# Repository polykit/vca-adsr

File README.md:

# Polykit VCA-ADSR

This repository contains schematics and PCB layout for a board with a VCA and an ADSR on it.

## Schematics

### VCA

### ADSR

## References

https://www.schmitzbits.de/adsr.html

https://yusynth.net/Modular/EN/VCA/index.html

https://kassu2000.blogspot.com/2015/10/vca.html

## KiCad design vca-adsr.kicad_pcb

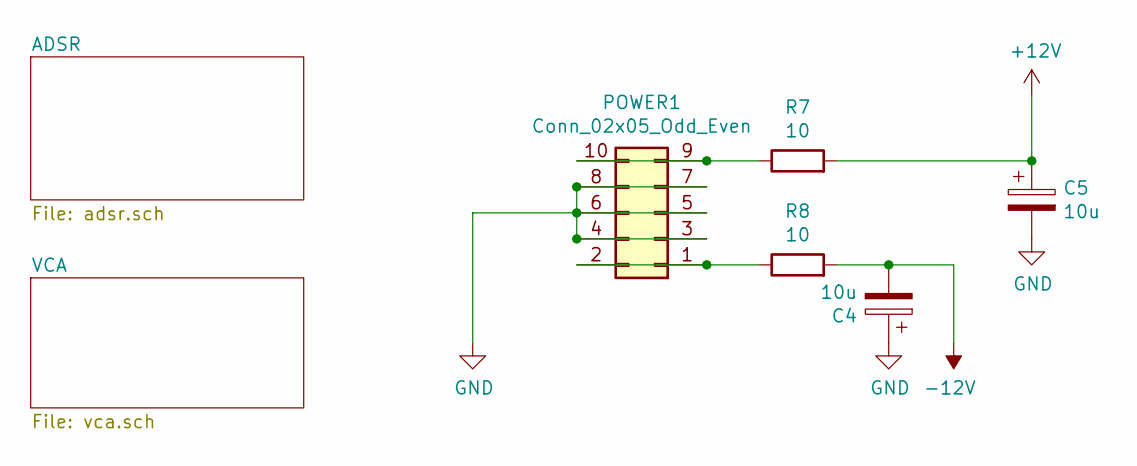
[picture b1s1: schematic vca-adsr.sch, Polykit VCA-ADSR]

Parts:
C4, C5: 10u; CP_Radial_D5.0mm_P2.50mm
POWER1: Conn_02x05_Odd_Even; IDC-Header_2x05_P2.54mm_Vertical
R7, R8: 10; R_Axial_DIN0207_L6.3mm_D2.5mm_P7.62mm_Horizontal

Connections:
+12V: C5.1, R7.2; also elsewhere on the board
-12V: C4.2, R8.2; also elsewhere on the board
GND: C4.1, C5.2, POWER1.3, POWER1.4, POWER1.5, POWER1.6, POWER1.7, POWER1.8; also elsewhere on the board
unnamed: POWER1.1, POWER1.2, R8.1
unnamed: POWER1.9, POWER1.10, R7.1

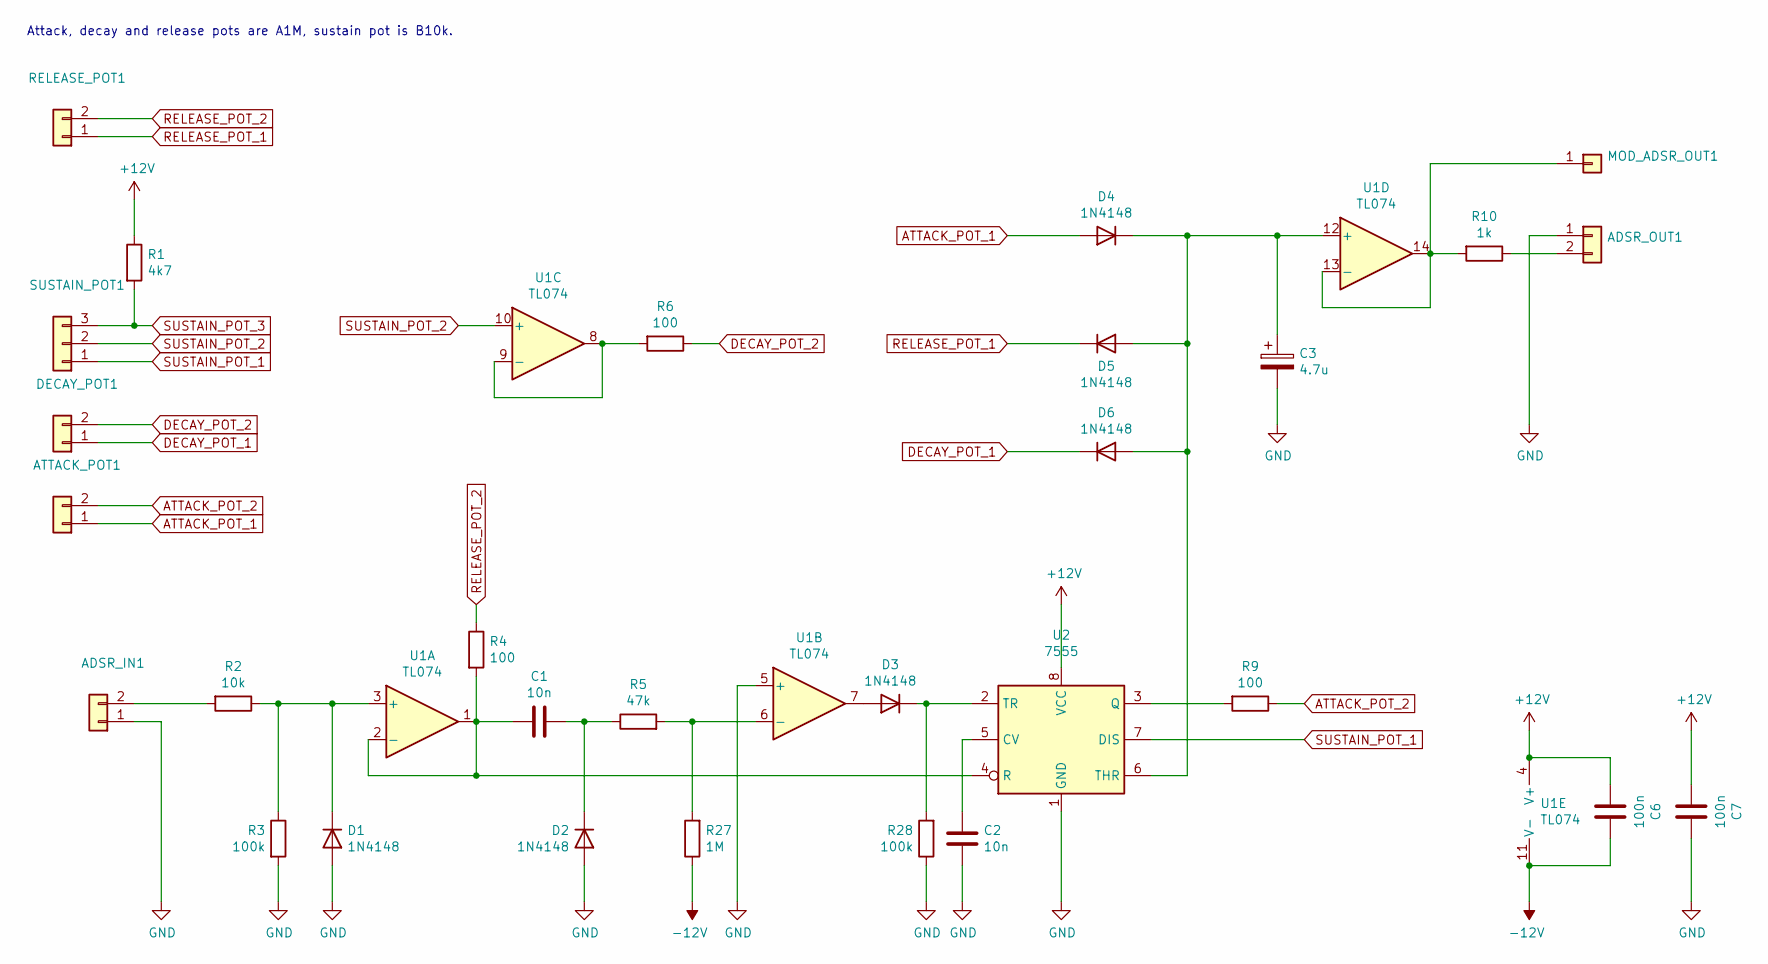
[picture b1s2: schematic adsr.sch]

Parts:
ADSR_IN1: Conn_01x02; Molex_KK-254_AE-6410-02A_1x02_P2.54mm_Vertical
ADSR_OUT1: Conn_01x02; Molex_KK-254_AE-6410-02A_1x02_P2.54mm_Vertical
ATTACK_POT1: Conn_01x02; Molex_KK-254_AE-6410-02A_1x02_P2.54mm_Vertical
C1, C2: 10n; C_Disc_D5.0mm_W2.5mm_P5.00mm
C3: 4.7u; CP_Radial_D5.0mm_P2.50mm
C6, C7: 100n; C_Disc_D5.0mm_W2.5mm_P5.00mm
D1, D2, D3, D4, D5, D6: 1N4148; D_DO-35_SOD27_P7.62mm_Horizontal
DECAY_POT1: Conn_01x02; Molex_KK-254_AE-6410-02A_1x02_P2.54mm_Vertical
MOD_ADSR_OUT1: Conn_01x01; Pin_D0.7mm_L6.5mm_W1.8mm_FlatFork
R1: 4k7; R_Axial_DIN0207_L6.3mm_D2.5mm_P7.62mm_Horizontal
R2: 10k; R_Axial_DIN0207_L6.3mm_D2.5mm_P7.62mm_Horizontal
R3: 100k; R_Axial_DIN0207_L6.3mm_D2.5mm_P7.62mm_Horizontal
R4: 100; R_Axial_DIN0207_L6.3mm_D2.5mm_P2.54mm_Vertical
R5: 47k; R_Axial_DIN0207_L6.3mm_D2.5mm_P2.54mm_Vertical
R6, R9: 100; R_Axial_DIN0207_L6.3mm_D2.5mm_P7.62mm_Horizontal
R10: 1k; R_Axial_DIN0207_L6.3mm_D2.5mm_P7.62mm_Horizontal
R27: 1M; R_Axial_DIN0207_L6.3mm_D2.5mm_P2.54mm_Vertical
R28: 100k; R_Axial_DIN0207_L6.3mm_D2.5mm_P2.54mm_Vertical
RELEASE_POT1: Conn_01x02; Molex_KK-254_AE-6410-02A_1x02_P2.54mm_Vertical
SUSTAIN_POT1: Conn_01x02; Molex_KK-254_AE-6410-03A_1x03_P2.54mm_Vertical
U1: TL074; DIP-14_W7.62mm_LongPads
U2: 7555; DIP-8_W7.62mm_LongPads

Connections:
+12V: C6.2, C7.2, R1.1, U1.4 (V+), U2.8 (VCC); also elsewhere on the board
-12V: C6.1, R27.1, U1.11 (V-); also elsewhere on the board
ATTACK_POT_1: ATTACK_POT1.1, D4.2 (A)
ATTACK_POT_2: ATTACK_POT1.2, R9.1
DECAY_POT_1: D6.1 (K), DECAY_POT1.1
DECAY_POT_2: DECAY_POT1.2, R6.1
GND: ADSR_IN1.1, ADSR_OUT1.1, C2.1, C3.2, C7.1, D1.2 (A), D2.2 (A), R3.2, R28.1, U1.5 (+), U2.1 (GND); also elsewhere on the board
unnamed: ADSR_IN1.2, R2.2
unnamed: ADSR_OUT1.2, R10.1
unnamed: C1.1, D2.1 (K), R5.1
unnamed: C1.2, R4.2, U1.1, U1.2 (-), U2.4 (R)
unnamed: C2.2, U2.5 (CV)
unnamed: C3.1, D4.1 (K), D5.2 (A), D6.2 (A), U1.12 (+), U2.6 (THR)
unnamed: D1.1 (K), R2.1, R3.1, U1.3 (+)
unnamed: D3.1 (K), R28.2, U2.2 (TR)
unnamed: D3.2 (A), U1.7
unnamed 20: MOD_ADSR_OUT1.1, R10.2, U1.13 (-), U1.14; also elsewhere on the board
unnamed: R6.2, U1.8, U1.9 (-)
unnamed: R9.2, U2.3 (Q)
unnamed: R5.2, R27.2, U1.6 (-)
RELEASE_POT_1: D5.1 (K), RELEASE_POT1.1
RELEASE_POT_2: R4.1, RELEASE_POT1.2
SUSTAIN_POT_1: SUSTAIN_POT1.1, U2.7 (DIS)
SUSTAIN_POT_2: SUSTAIN_POT1.2, U1.10 (+)
SUSTAIN_POT_3: R1.2, SUSTAIN_POT1.3

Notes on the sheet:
Attack, decay and release pots are A1M, sustain pot is B10k.

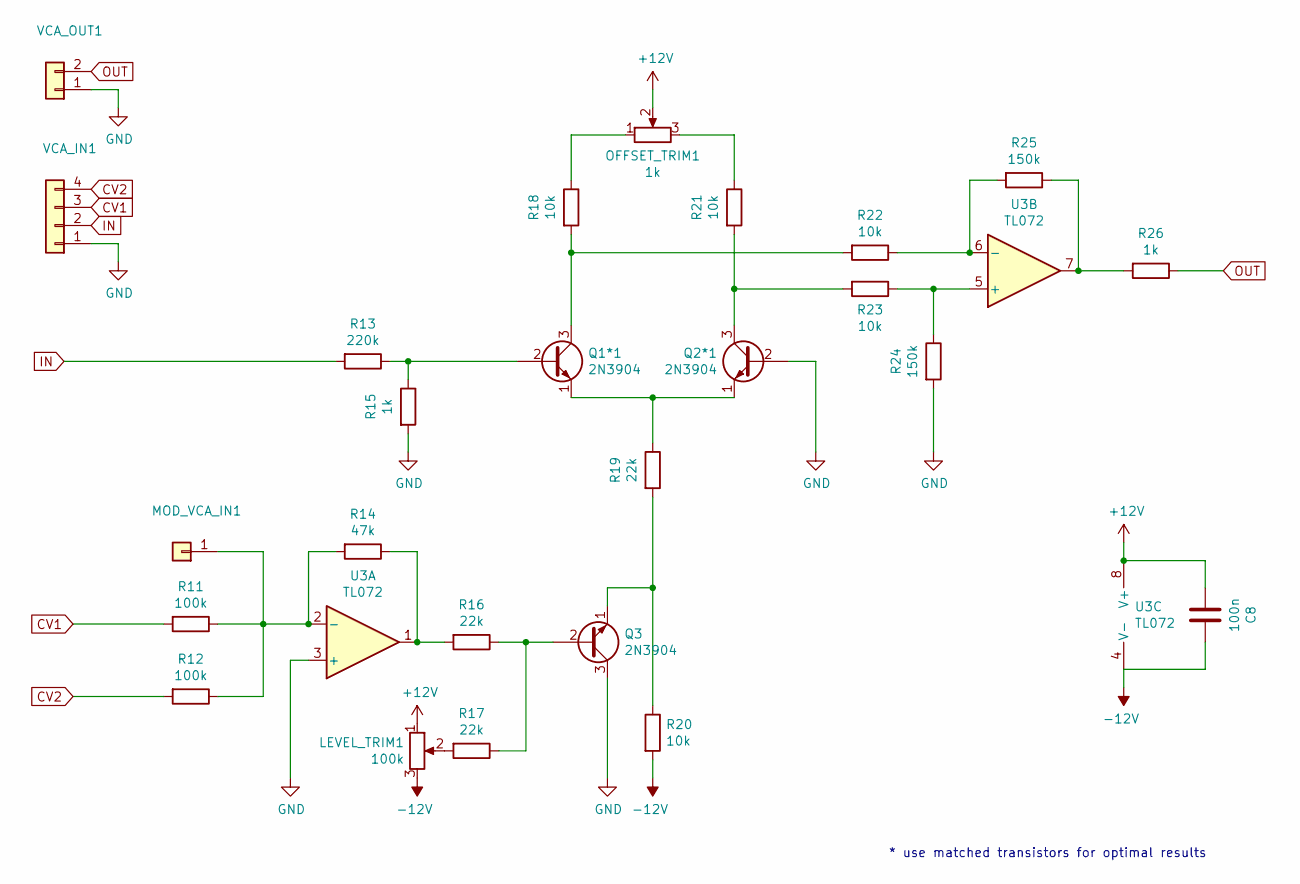
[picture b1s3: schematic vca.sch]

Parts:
C8: 100n; C_Disc_D5.0mm_W2.5mm_P5.00mm
LEVEL_TRIM1: 100k; Potentiometer_ACP_CA9-H5_Horizontal
MOD_VCA_IN1: Conn_01x01; Pin_D0.7mm_L6.5mm_W1.8mm_FlatFork
OFFSET_TRIM1: 1k; Potentiometer_ACP_CA9-H5_Horizontal
Q1*1, Q2*1, Q3: 2N3904; TO-92_Inline_Wide
R11, R12: 100k; R_Axial_DIN0207_L6.3mm_D2.5mm_P7.62mm_Horizontal
R13: 220k; R_Axial_DIN0207_L6.3mm_D2.5mm_P7.62mm_Horizontal
R14: 47k; R_Axial_DIN0207_L6.3mm_D2.5mm_P7.62mm_Horizontal
R15, R26: 1k; R_Axial_DIN0207_L6.3mm_D2.5mm_P7.62mm_Horizontal
R16, R17, R19: 22k; R_Axial_DIN0207_L6.3mm_D2.5mm_P7.62mm_Horizontal
R18, R20, R21, R22, R23: 10k; R_Axial_DIN0207_L6.3mm_D2.5mm_P7.62mm_Horizontal
R24, R25: 150k; R_Axial_DIN0207_L6.3mm_D2.5mm_P7.62mm_Horizontal
U3: TL072; DIP-8_W7.62mm_Socket_LongPads
VCA_IN1: Conn_01x04; Molex_KK-254_AE-6410-04A_1x04_P2.54mm_Vertical
VCA_OUT1: Conn_01x02; Molex_KK-254_AE-6410-02A_1x02_P2.54mm_Vertical

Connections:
+12V: C8.2, LEVEL_TRIM1.1, OFFSET_TRIM1.2, U3.8 (V+); also elsewhere on the board
-12V: C8.1, LEVEL_TRIM1.3, R20.2, U3.4 (V-); also elsewhere on the board
CV1: R11.2, VCA_IN1.3
CV2: R12.2, VCA_IN1.4
GND: Q2*1.2 (B), Q3.3 (C), R15.2, R24.2, U3.3 (+), VCA_IN1.1, VCA_OUT1.1; also elsewhere on the board
IN: R13.2, VCA_IN1.2
unnamed: LEVEL_TRIM1.2, R17.2
unnamed 21: MOD_VCA_IN1.1, R11.1, R12.1, R14.2, U3.2 (-); also elsewhere on the board
unnamed: OFFSET_TRIM1.1, R18.1
unnamed: OFFSET_TRIM1.3, R21.1
unnamed: Q1*1.1 (E), Q2*1.1 (E), R19.1
unnamed: Q1*1.2 (B), R13.1, R15.1
unnamed: Q1*1.3 (C), R18.2, R22.2
unnamed: Q2*1.3 (C), R21.2, R23.2
unnamed: Q3.1 (E), R19.2, R20.1
unnamed: Q3.2 (B), R16.1, R17.1
unnamed: R14.1, R16.2, U3.1
unnamed: R22.1, R25.2, U3.6 (-)
unnamed: R23.1, R24.1, U3.5 (+)
unnamed: R25.1, R26.2, U3.7
OUT: R26.1, VCA_OUT1.2

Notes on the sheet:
* use matched transistors for optimal results

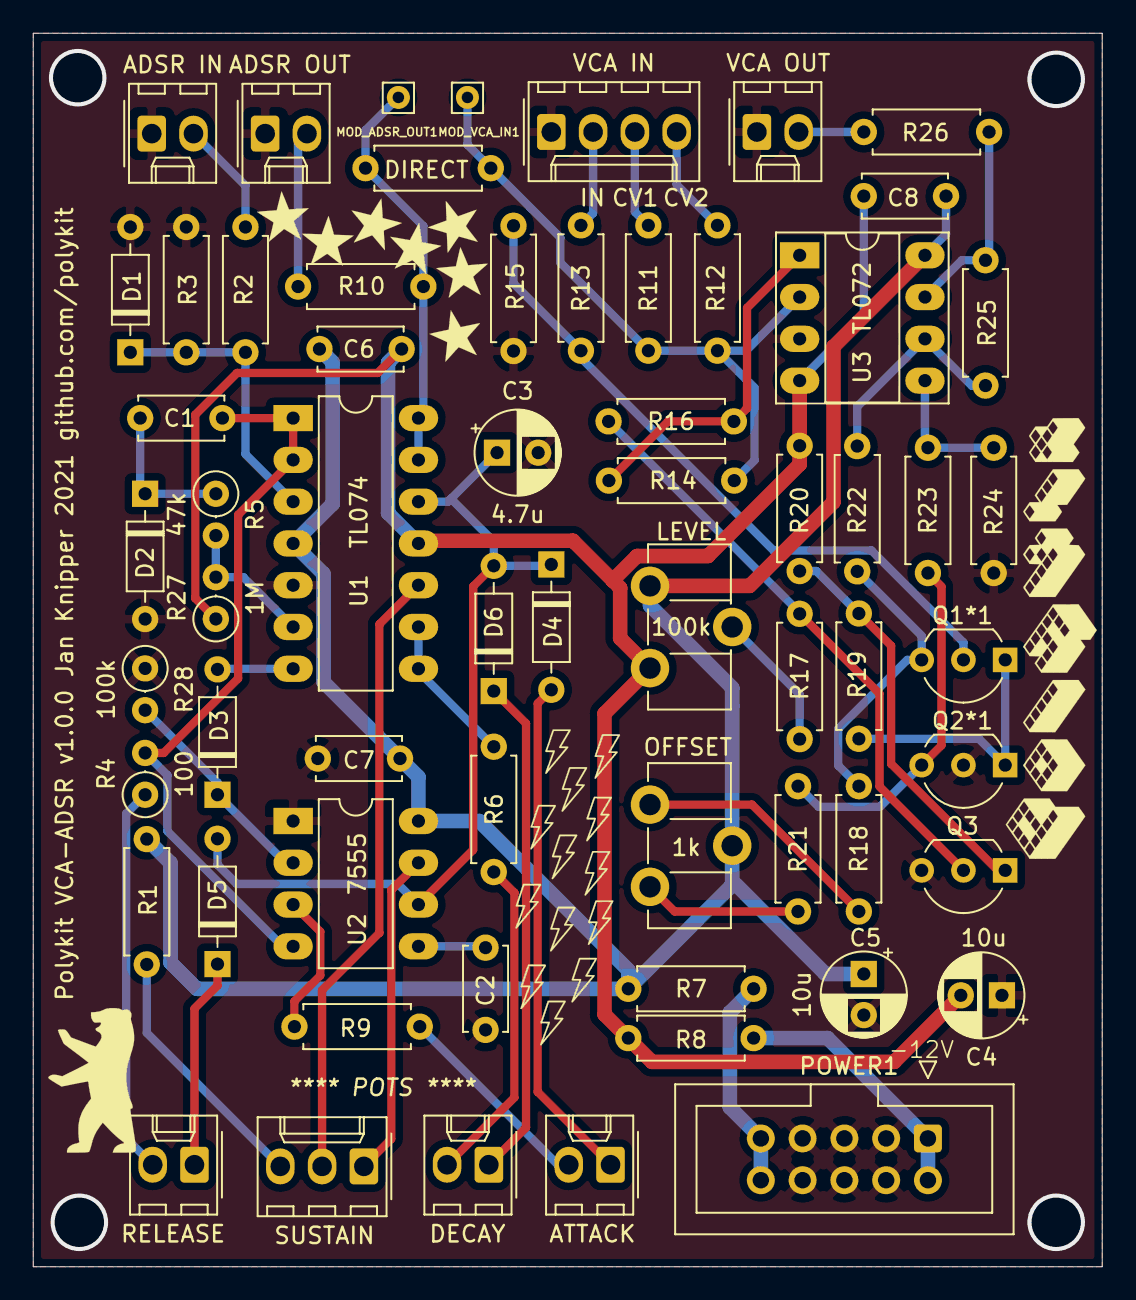
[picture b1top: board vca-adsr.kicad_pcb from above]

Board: 2 copper layers, 65.0 x 75.0 mm, 62 parts (0 on the bottom side), 45 nets.

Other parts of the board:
DIRECT: R_Axial_DIN0207_L6.3mm_D2.5mm_P7.62mm_Horizontal

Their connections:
unnamed 20: DIRECT.1; also elsewhere on the board
unnamed 21: DIRECT.2; also elsewhere on the board

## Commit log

2021-03-10 Initial import
2021-06-18 Fix envelope trigger
2021-06-18 Update adsr schematics
